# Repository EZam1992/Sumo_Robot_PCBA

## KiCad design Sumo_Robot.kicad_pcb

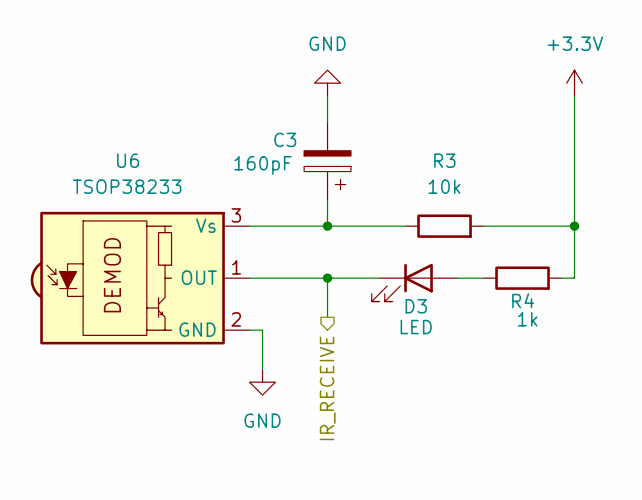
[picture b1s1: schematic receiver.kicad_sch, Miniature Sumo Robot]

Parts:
C3: 160pF; C_1210_3225Metric
D3: LED; LED_1210_3225Metric
R3: 10k; R_1210_3225Metric
R4: 1k; R_1210_3225Metric
U6: TSOP38233; Vishay_MINICAST-3Pin

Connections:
+3.3V: R3.2, R4.2; also elsewhere on the board
/InfraredReceiver/IR_RECEIVE: D3.1 (K), U6.1 (OUT); also elsewhere on the board
GND: C3.2, U6.2 (GND); also elsewhere on the board
unnamed: D3.2 (A), R4.1
unnamed: C3.1, R3.1, U6.3 (Vs)

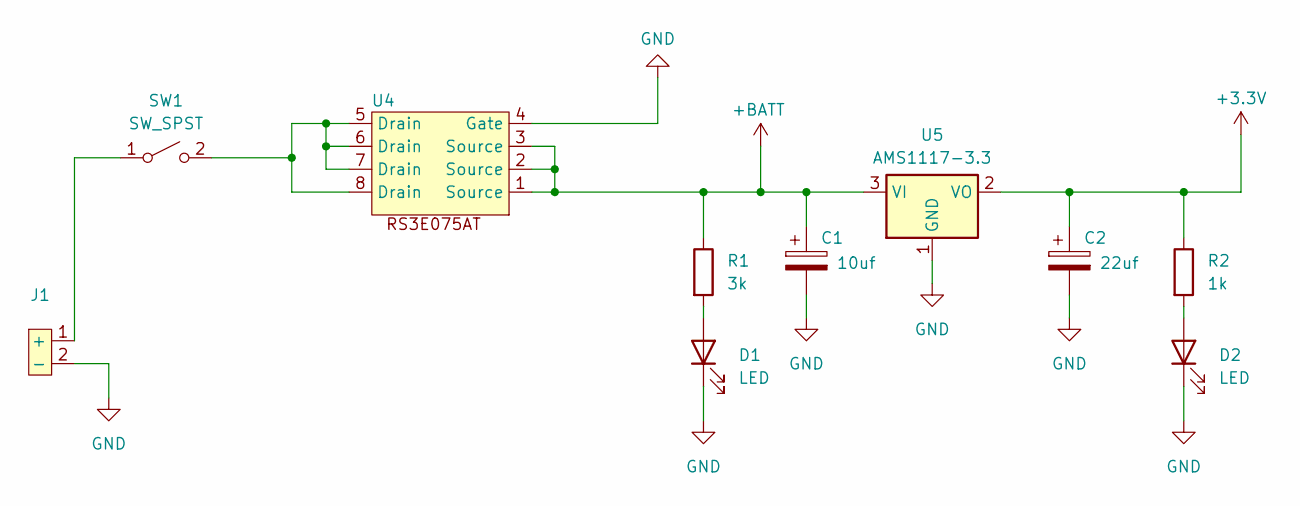
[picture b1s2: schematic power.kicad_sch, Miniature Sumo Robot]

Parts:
C1: 10uf; C_1210_3225Metric
C2: 22uf; C_1210_3225Metric
D1, D2: LED; LED_1210_3225Metric
J1: AMASS_XT60-F_1x02_P7.20mm_Vertical
R1: 3k; R_1210_3225Metric
R2: 1k; R_1210_3225Metric
SW1: SW_SPST; SW_DIP_SPSTx01_Slide_9.78x4.72mm_W8.61mm_P2.54mm
U4: SOP-8_3.76x4.96mm_P1.27mm
U5: AMS1117-3.3; SOT-223

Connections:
+3.3V: C2.1, R2.1, U5.2 (VO); also elsewhere on the board
+BATT: C1.1, R1.1, U4.1 (Source), U4.2 (Source), U4.3 (Source), U5.3 (VI); also elsewhere on the board
GND: C1.2, C2.2, D1.1 (K), D2.1 (K), J1.2 (-), U4.4 (Gate), U5.1 (GND); also elsewhere on the board
unnamed: D1.2 (A), R1.2
unnamed: D2.2 (A), R2.2
unnamed: J1.1 (+), SW1.1 (A)
unnamed: SW1.2 (B), U4.5 (Drain), U4.6 (Drain), U4.7 (Drain), U4.8 (Drain)

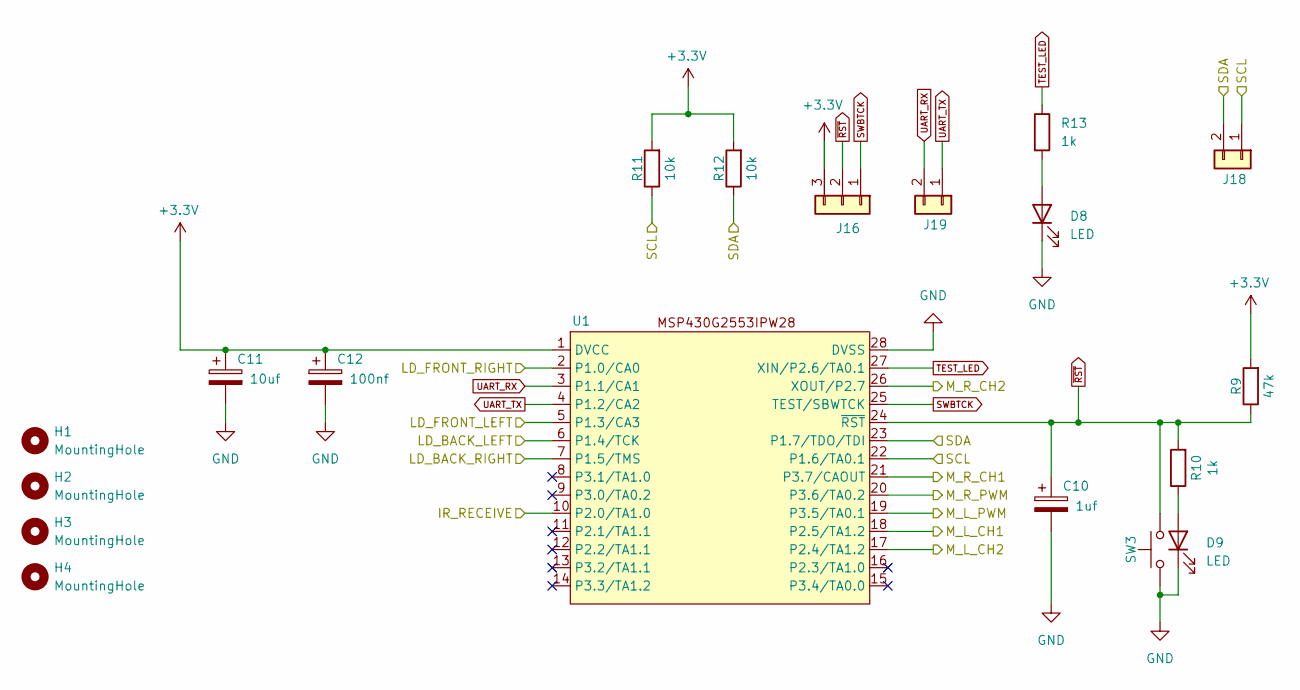
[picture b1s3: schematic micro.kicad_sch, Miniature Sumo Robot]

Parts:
C10: 1uf; C_1210_3225Metric
C11: 10uf; C_1210_3225Metric
C12: 100nf; C_1210_3225Metric
D8, D9: LED; LED_1210_3225Metric
H1, H2, H3, H4: MountingHole; MountingHole_2.5mm_Pad
J16: Conn_01x03; PinHeader_1x03_P1.00mm_Vertical
J18, J19: Conn_01x02; PinHeader_1x02_P1.00mm_Vertical
R9: 47k; R_1210_3225Metric
R10, R13: 1k; R_1210_3225Metric
R11, R12: 10k; R_1210_3225Metric
SW3: SW_Omron_B3FS; SW_SPST_Omron_B3FS-100xP
U1: TSSOP-28_4.4x9.7mm_P0.65mm

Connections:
+3.3V: C11.1, C12.1, J16.3, R9.2, R11.2, R12.2, U1.1 (DVCC); also elsewhere on the board
/InfraredReceiver/IR_RECEIVE: U1.10 (P2.0/TA1.0); also elsewhere on the board
/LeftMotor/M_R_CH1: U1.21 (P3.7/CAOUT); also elsewhere on the board
/LeftMotor/M_R_CH2: U1.26 (XOUT/P2.7); also elsewhere on the board
/LeftMotor/M_R_PWM: U1.20 (P3.6/TA0.2); also elsewhere on the board
/LineSensors/LD_BACK_LEFT: U1.6 (P1.4/TCK); also elsewhere on the board
/LineSensors/LD_BACK_RIGHT: U1.7 (P1.5/TMS); also elsewhere on the board
/LineSensors/LD_FRONT_LEFT: U1.5 (P1.3/CA3); also elsewhere on the board
/LineSensors/LD_FRONT_RIGHT: U1.2 (P1.0/CA0); also elsewhere on the board
/Microcontroller/M_L_CH1: U1.18 (P2.5/TA1.2); also elsewhere on the board
/Microcontroller/M_L_CH2: U1.17 (P2.4/TA1.2); also elsewhere on the board
/Microcontroller/M_L_PWM: U1.19 (P3.5/TA0.1); also elsewhere on the board
/Microcontroller/SCL: J18.1, R11.1, U1.22 (P1.6/TA0.1); also elsewhere on the board
/Microcontroller/SDA: J18.2, R12.1, U1.23 (P1.7/TDO/TDI); also elsewhere on the board
GND: C10.2, C11.2, C12.2, D8.1 (K), D9.1 (K), SW3.1, U1.28 (DVSS); also elsewhere on the board
unnamed: D8.2 (A), R13.2
unnamed: D9.2 (A), R10.1
SWBTCK: J16.1, U1.25 (TEST/SBWTCK)
TEST_LED: R13.1, U1.27 (XIN/P2.6/TA0.1)
UART_RX: J19.2, U1.3 (P1.1/CA1)
UART_TX: J19.1, U1.4 (P1.2/CA2)
~RST: C10.1, J16.2, R9.1, R10.2, SW3.2, U1.24 (~RST)

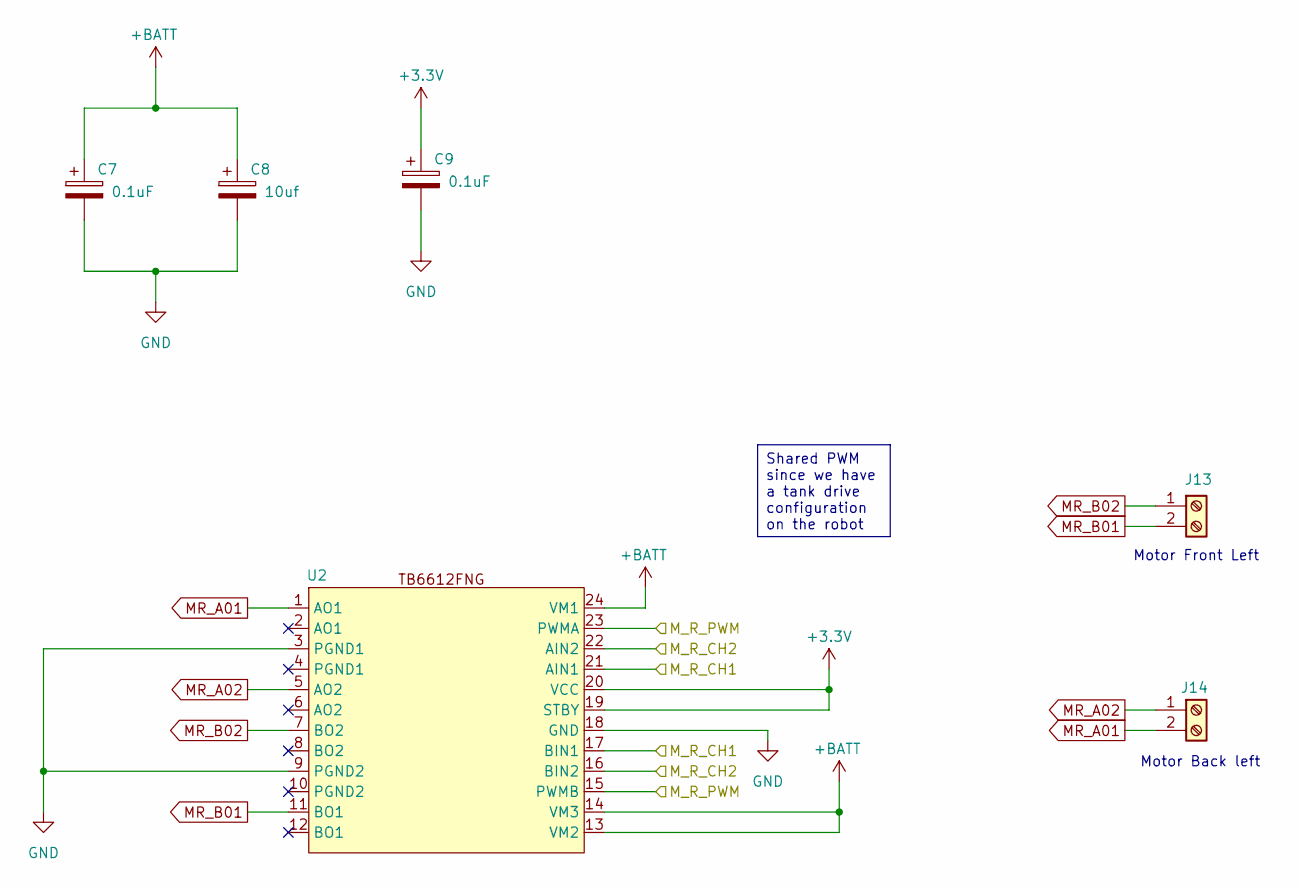
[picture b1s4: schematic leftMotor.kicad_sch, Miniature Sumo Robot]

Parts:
C7, C9: 0.1uF; C_1210_3225Metric
C8: 10uf; C_1210_3225Metric
J13: TerminalBlock_Phoenix_MKDS-1,5-2_1x02_P5.00mm_Horizontal
J14: Screw_Terminal_01x02; TerminalBlock_Phoenix_MKDS-1,5-2_1x02_P5.00mm_Horizontal
U2: SSOP-24_5.3x8.2mm_P0.65mm

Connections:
+3.3V: C9.1, U2.19 (STBY), U2.20 (VCC); also elsewhere on the board
+BATT: C7.1, C8.1, U2.13 (VM2), U2.14 (VM3), U2.24 (VM1); also elsewhere on the board
/LeftMotor/M_R_CH1: U2.17 (BIN1), U2.21 (AIN1); also elsewhere on the board
/LeftMotor/M_R_CH2: U2.16 (BIN2), U2.22 (AIN2); also elsewhere on the board
/LeftMotor/M_R_PWM: U2.15 (PWMB), U2.23 (PWMA); also elsewhere on the board
GND: C7.2, C8.2, C9.2, U2.3 (PGND1), U2.9 (PGND2), U2.18 (GND); also elsewhere on the board
MR_A01: J14.2, U2.1 (AO1)
MR_A02: J14.1, U2.5 (AO2)
MR_B01: J13.2, U2.11 (BO1)
MR_B02: J13.1, U2.7 (BO2)

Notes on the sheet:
Motor Front Left
Motor Back left
Shared PWM since we have a tank drive configuration on the robot

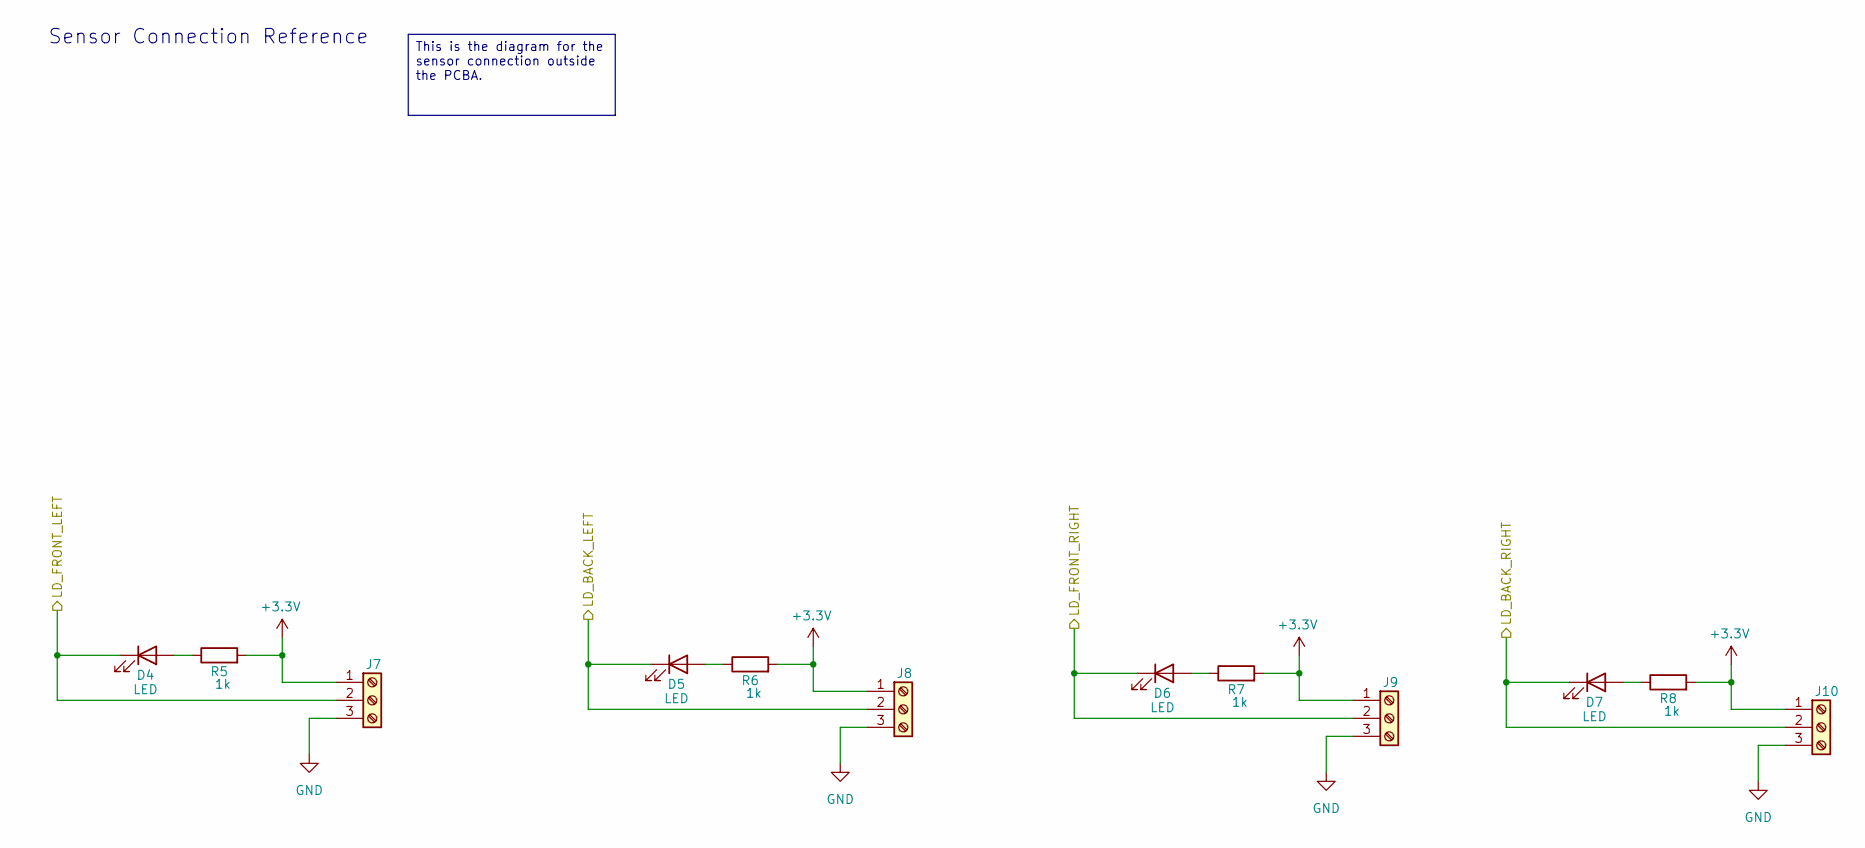
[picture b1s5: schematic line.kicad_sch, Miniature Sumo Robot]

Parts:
D4, D5, D6, D7: LED; LED_1210_3225Metric
J7, J8, J9, J10: Screw_Terminal_01x03; TerminalBlock_Phoenix_MKDS-1,5-3_1x03_P5.00mm_Horizontal
R5, R6, R7, R8: 1k; R_1210_3225Metric

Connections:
+3.3V: J7.1, J8.1, J9.1, J10.1, R5.2, R6.2, R7.2, R8.2; also elsewhere on the board
/LineSensors/LD_BACK_LEFT: D5.1 (K), J8.2; also elsewhere on the board
/LineSensors/LD_BACK_RIGHT: D7.1 (K), J10.2; also elsewhere on the board
/LineSensors/LD_FRONT_LEFT: D4.1 (K), J7.2; also elsewhere on the board
/LineSensors/LD_FRONT_RIGHT: D6.1 (K), J9.2; also elsewhere on the board
GND: J7.3, J8.3, J9.3, J10.3; also elsewhere on the board
unnamed: D4.2 (A), R5.1
unnamed: D5.2 (A), R6.1
unnamed: D6.2 (A), R7.1
unnamed: D7.2 (A), R8.1

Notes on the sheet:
Sensor Connection Reference
This is the diagram for the sensor connection outside the PCBA.

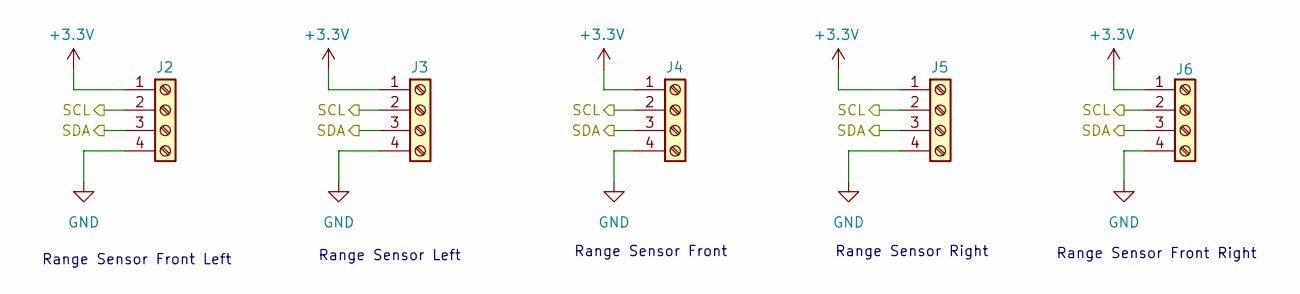
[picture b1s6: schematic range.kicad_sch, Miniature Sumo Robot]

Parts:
J2, J3, J4, J5, J6: Screw_Terminal_01x04; TerminalBlock_Phoenix_MKDS-1,5-4_1x04_P5.00mm_Horizontal

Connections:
+3.3V: J2.1, J3.1, J4.1, J5.1, J6.1; also elsewhere on the board
/Microcontroller/SCL: J2.2, J3.2, J4.2, J5.2, J6.2; also elsewhere on the board
/Microcontroller/SDA: J2.3, J3.3, J4.3, J5.3, J6.3; also elsewhere on the board
GND: J2.4, J3.4, J4.4, J5.4, J6.4; also elsewhere on the board

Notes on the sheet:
Range Sensor Left
Range Sensor Front
Range Sensor Right
Range Sensor Front Left
Range Sensor Front Right

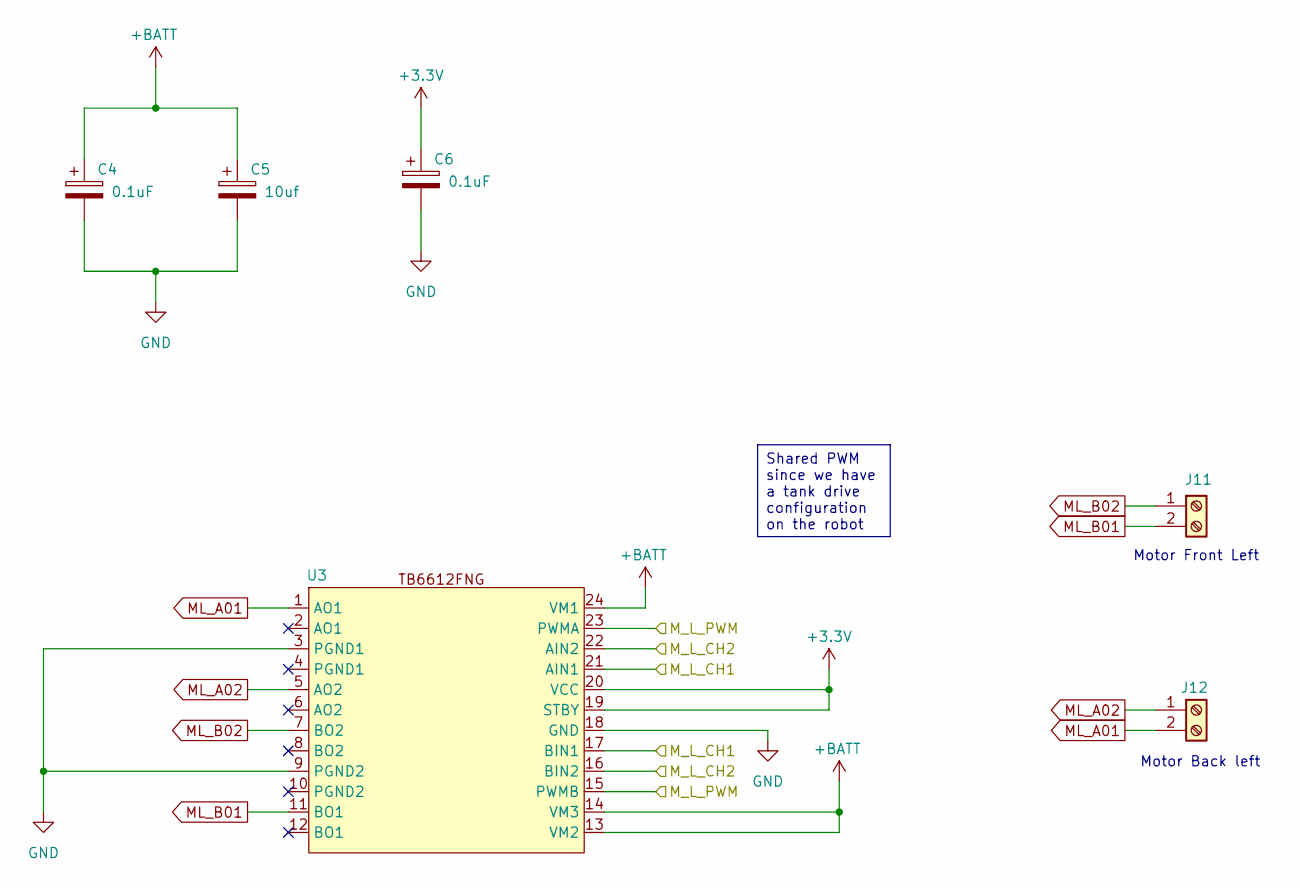
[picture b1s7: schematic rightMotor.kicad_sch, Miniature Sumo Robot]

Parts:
C4, C6: 0.1uF; C_1210_3225Metric
C5: 10uf; C_1210_3225Metric
J11: TerminalBlock_Phoenix_MKDS-1,5-2_1x02_P5.00mm_Horizontal
J12: Screw_Terminal_01x02; TerminalBlock_Phoenix_MKDS-1,5-2_1x02_P5.00mm_Horizontal
U3: SSOP-24_5.3x8.2mm_P0.65mm

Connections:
+3.3V: C6.1, U3.19 (STBY), U3.20 (VCC); also elsewhere on the board
+BATT: C4.1, C5.1, U3.13 (VM2), U3.14 (VM3), U3.24 (VM1); also elsewhere on the board
/Microcontroller/M_L_CH1: U3.17 (BIN1), U3.21 (AIN1); also elsewhere on the board
/Microcontroller/M_L_CH2: U3.16 (BIN2), U3.22 (AIN2); also elsewhere on the board
/Microcontroller/M_L_PWM: U3.15 (PWMB), U3.23 (PWMA); also elsewhere on the board
GND: C4.2, C5.2, C6.2, U3.3 (PGND1), U3.9 (PGND2), U3.18 (GND); also elsewhere on the board
ML_A01: J12.2, U3.1 (AO1)
ML_A02: J12.1, U3.5 (AO2)
ML_B01: J11.2, U3.11 (BO1)
ML_B02: J11.1, U3.7 (BO2)

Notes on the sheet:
Motor Back left
Motor Front Left
Shared PWM since we have a tank drive configuration on the robot

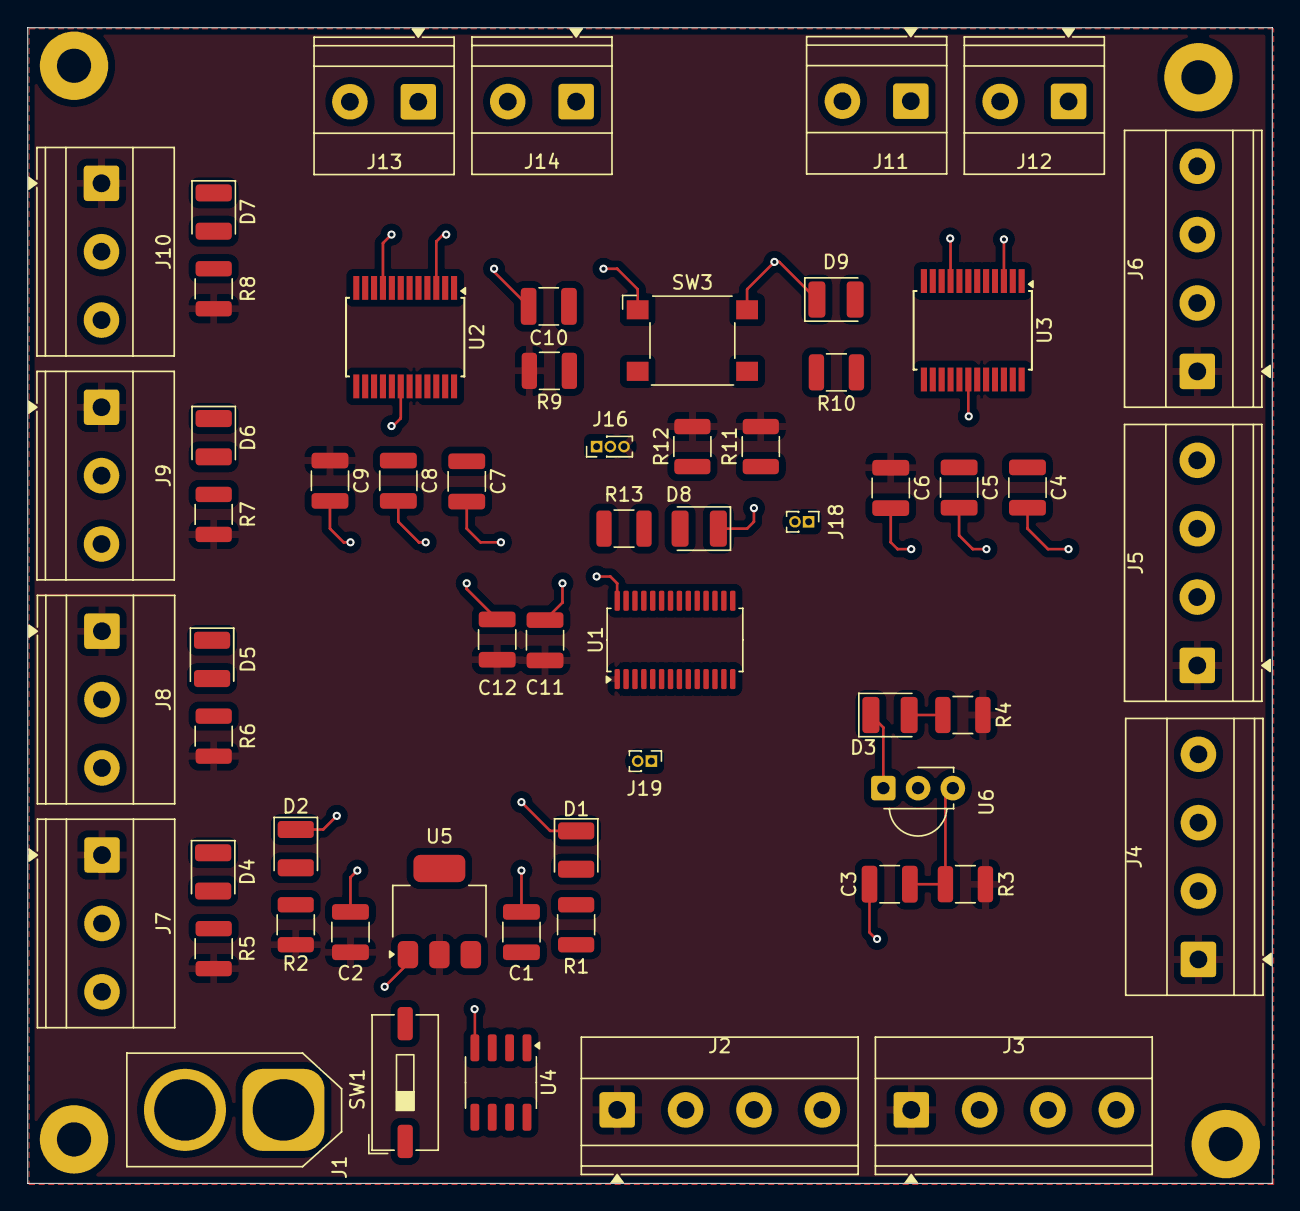
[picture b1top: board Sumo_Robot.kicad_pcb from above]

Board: 4 copper layers, 91.0 x 84.5 mm, 63 parts (0 on the bottom side), 41 nets.

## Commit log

2025-04-06 added hierarchical schematic
2025-05-20 modifying from work PC
2025-05-20 commit from home PC
2025-06-03 added mounting holes
2025-06-07 adding symbol libraries
2025-06-08 Updated MCU symbol
2025-06-08 added mcu to schematics
2025-06-08 updated symbol library
2025-06-08 updated motor driver files
2025-06-08 added symbols
2025-06-14 added power connectors and modified power shematic
2025-06-14 updated poer and range sensor scheamtics
2025-06-18 added I2C lines
2025-06-25 added LDO
2025-06-26 added IR receiver circuit
2025-07-10 added more details to schematics
2025-07-12 updated logic for MCU
2025-07-18 started adding DC Motor controller logic
2025-07-24 added motor functionality to the MCU
2025-07-26 updated MCU COMMS
2025-07-29 updated MCU schematic
2025-07-29 removed mechanical sheet
2025-08-07 finalized schematic
2025-08-08 minor update to an MCU circuit
2025-08-23 started layout of Rev A
2025-09-10 added all footprints and step files to components
2025-09-11 continued layout
2025-09-12 continuing layout
2025-09-27 updated infomration on schematic; started working on layout
2025-09-28 layout updates
2025-10-30 Updated PCB Layers and Schematics
2025-10-31 layout advancing
2025-10-31 advancing layout
2025-10-31 updated layout
2025-10-31 updating layout
2026-01-18 updating layers
2026-01-19 rethinking the layout
2026-01-19 layout rethinking
2026-01-20 updating pcb layout
